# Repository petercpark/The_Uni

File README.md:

# The Uni Board
The uni-body split ortholinear keyboard for stenography, or the Uni for short. By Peter C Park. This is the pro micro version. I used KiCad Nightly Release so the kicad files are not compatible with older version.

Buy it now at [StenoKeyboards.com](https://www.stenokeyboards.com/).

## Product
If you are going DIY with this, here are the materials you need:
* The Uni PCB x 1 (diodes will come pre-assembled)
* Arduino Pro Micro x 1
* Switches x 28
* Keycaps x 28
* Willingness to solder x 1

If you want me to assemble here are the materials you need:
* money

## Arduino
The arduino you should use is the Pro Micro. You can also use other microcontrollers with same footprints such as the Elite C.

## Switches
Nearly any switch is compatible with the v2. The board has a footprint that accomodates for mx, alps, and choc v1 style switches.

## Keycaps
The best keycaps to use are the OEM R3 keycaps with one of the rows inverted to reduce the gap in the middle.
I used to recommend 3d printing your caps but OEM R3 caps are better. There are other flat keycaps for mx style switches at pimpmykeyboard.com called f10 keycaps. There is also a slightly less flatter version called the G20 keycaps on their store and people have used them for steno.

## Soldering
All you have to solder are the switches and pro micro if you get the pcb with the diodes assembled. If not you'll have to solder the smd diodes yourself. Check the BOM file for the necessary materials.

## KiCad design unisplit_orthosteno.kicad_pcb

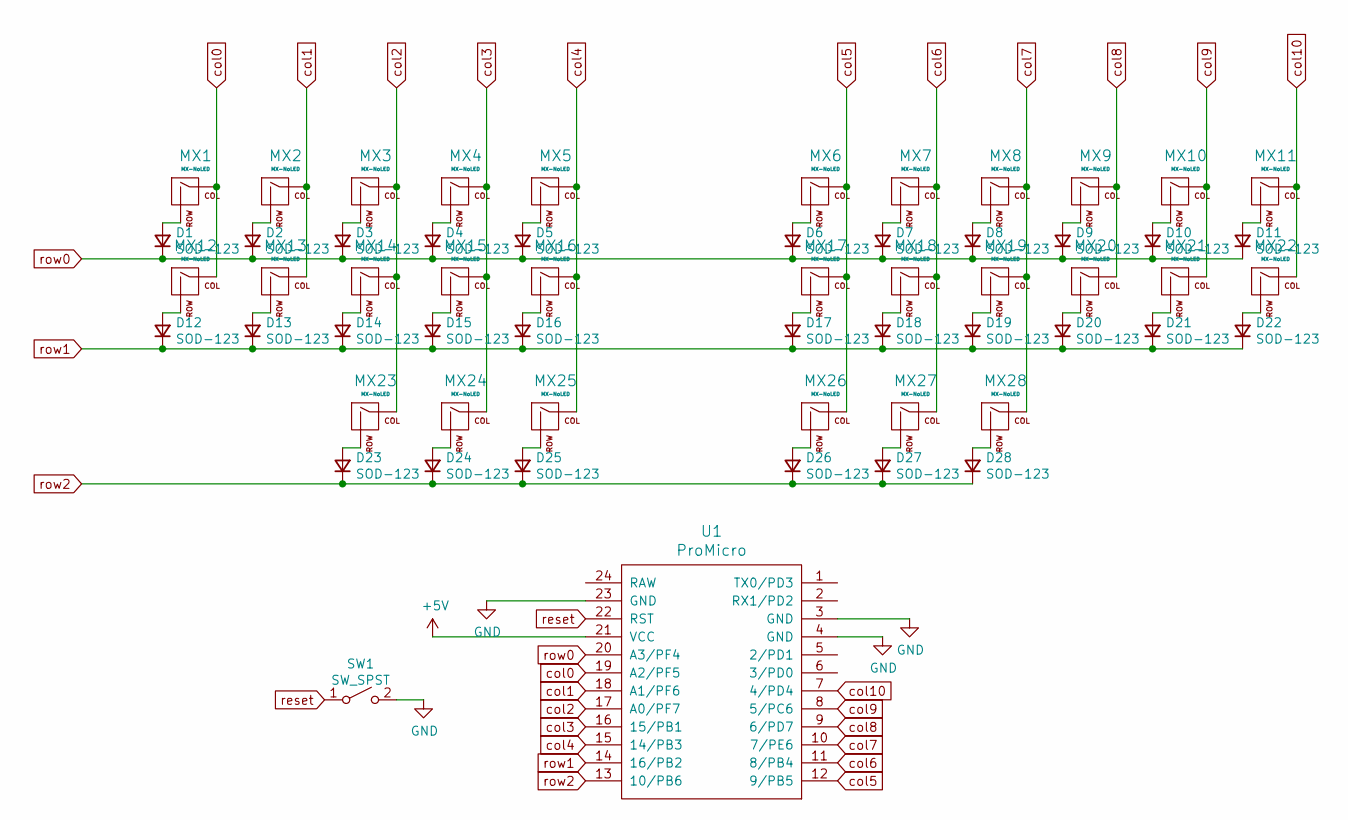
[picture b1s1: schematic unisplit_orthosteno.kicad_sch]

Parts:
D1, D2, D3, D4, D5, D6, D7, D8, D9, D10, D11, D12, D13, D15, D16, D17, D18, D19, D20, D21, D22, D23, D24, D25, D26, D27, D28: SOD-123; D_SOD123; LCSC C81598
D14: SOD-123; D_SOD123
MX1, MX2, MX3, MX4, MX5, MX6, MX7, MX8, MX9, MX10, MX11, MX12, MX13, MX14, MX15, MX16, MX17, MX18, MX19, MX20, MX21, MX22, MX23, MX24, MX25, MX26, MX27, MX28: MX-NoLED; MX-Alps-Choc-1U-NoLED
SW1: SW_SPST; SW_SPST_TL3342
U1: ProMicro; ArduinoProMicro

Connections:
+5V: U1.21 (VCC)
GND: SW1.2 (B), U1.3 (GND), U1.4 (GND), U1.23 (GND)
unnamed: D1.2 (A), MX1.2 (ROW)
unnamed: D2.2 (A), MX2.2 (ROW)
unnamed: D3.2 (A), MX3.2 (ROW)
unnamed: D4.2 (A), MX4.2 (ROW)
unnamed: D5.2 (A), MX5.2 (ROW)
unnamed: D6.2 (A), MX6.2 (ROW)
unnamed: D7.2 (A), MX7.2 (ROW)
unnamed: D8.2 (A), MX8.2 (ROW)
unnamed: D9.2 (A), MX9.2 (ROW)
unnamed: D10.2 (A), MX10.2 (ROW)
unnamed: D11.2 (A), MX11.2 (ROW)
unnamed: D12.2 (A), MX12.2 (ROW)
unnamed: D13.2 (A), MX13.2 (ROW)
unnamed: D14.2 (A), MX14.2 (ROW)
unnamed: D15.2 (A), MX15.2 (ROW)
unnamed: D16.2 (A), MX16.2 (ROW)
unnamed: D17.2 (A), MX17.2 (ROW)
unnamed: D18.2 (A), MX18.2 (ROW)
unnamed: D19.2 (A), MX19.2 (ROW)
unnamed: D20.2 (A), MX20.2 (ROW)
unnamed: D21.2 (A), MX21.2 (ROW)
unnamed: D22.2 (A), MX22.2 (ROW)
unnamed: D23.2 (A), MX23.2 (ROW)
unnamed: D24.2 (A), MX24.2 (ROW)
unnamed: D25.2 (A), MX25.2 (ROW)
unnamed: D26.2 (A), MX26.2 (ROW)
unnamed: D27.2 (A), MX27.2 (ROW)
unnamed: D28.2 (A), MX28.2 (ROW)
col0: MX1.1 (COL), MX12.1 (COL), U1.19 (A2/PF5)
col1: MX2.1 (COL), MX13.1 (COL), U1.18 (A1/PF6)
col2: MX3.1 (COL), MX14.1 (COL), MX23.1 (COL), U1.17 (A0/PF7)
col3: MX4.1 (COL), MX15.1 (COL), MX24.1 (COL), U1.16 (15/PB1)
col4: MX5.1 (COL), MX16.1 (COL), MX25.1 (COL), U1.15 (14/PB3)
col5: MX6.1 (COL), MX17.1 (COL), MX26.1 (COL), U1.12 (9/PB5)
col6: MX7.1 (COL), MX18.1 (COL), MX27.1 (COL), U1.11 (8/PB4)
col7: MX8.1 (COL), MX19.1 (COL), MX28.1 (COL), U1.10 (7/PE6)
col8: MX9.1 (COL), MX20.1 (COL), U1.9 (6/PD7)
col9: MX10.1 (COL), MX21.1 (COL), U1.8 (5/PC6)
col10: MX11.1 (COL), MX22.1 (COL), U1.7 (4/PD4)
reset: SW1.1 (A), U1.22 (RST)
row0: D1.1 (K), D2.1 (K), D3.1 (K), D4.1 (K), D5.1 (K), D6.1 (K), D7.1 (K), D8.1 (K), D9.1 (K), D10.1 (K), D11.1 (K), U1.20 (A3/PF4)
row1: D12.1 (K), D13.1 (K), D14.1 (K), D15.1 (K), D16.1 (K), D17.1 (K), D18.1 (K), D19.1 (K), D20.1 (K), D21.1 (K), D22.1 (K), U1.14 (16/PB2)
row2: D23.1 (K), D24.1 (K), D25.1 (K), D26.1 (K), D27.1 (K), D28.1 (K), U1.13 (10/PB6)

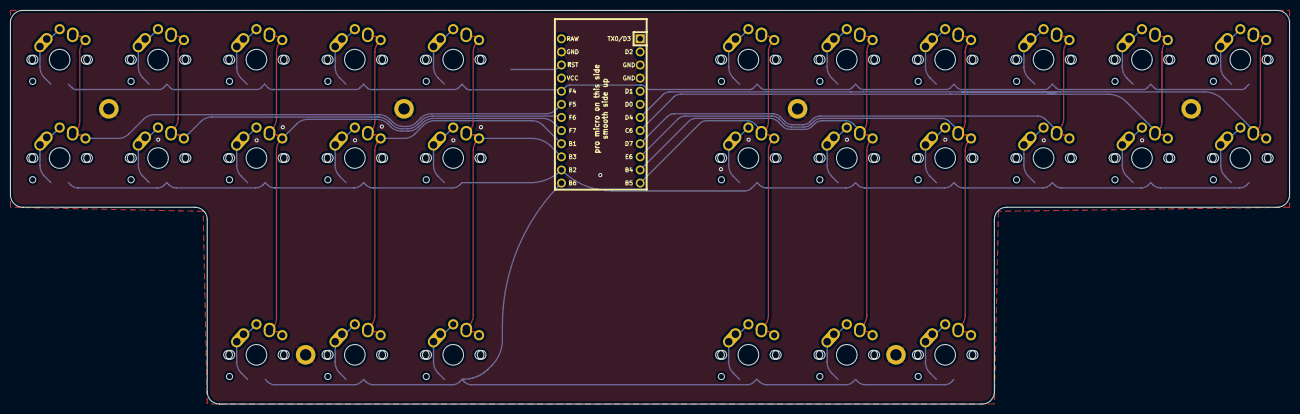
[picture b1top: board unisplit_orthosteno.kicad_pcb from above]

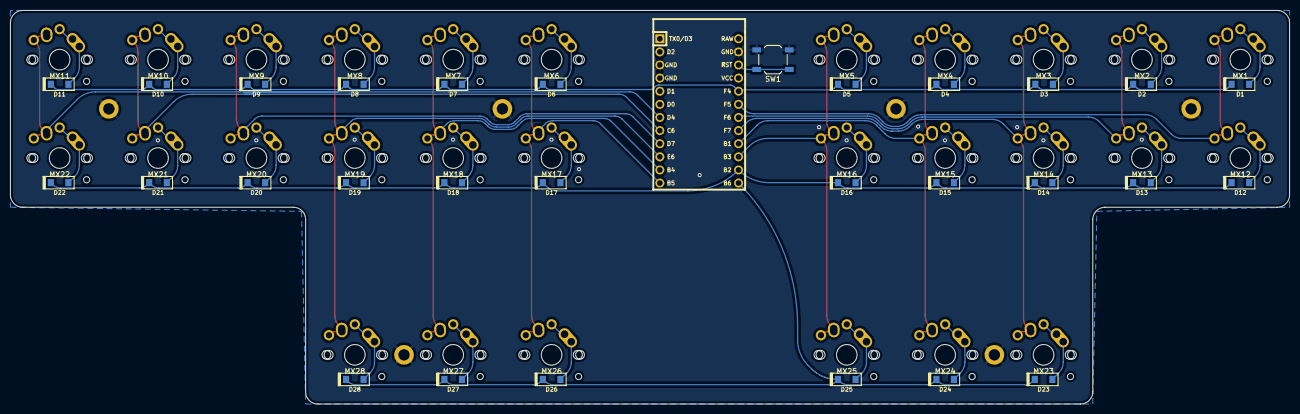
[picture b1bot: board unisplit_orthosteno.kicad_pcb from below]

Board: 2 copper layers, 247.6 x 76.2 mm, 58 parts (30 on the bottom side), 44 nets.

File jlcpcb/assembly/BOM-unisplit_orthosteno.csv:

Comment,Designator,Footprint,LCSC
SW_SPST,SW1,SW_SPST_TL3342,C318884
SOD-123,"D1,D10,D11,D12,D13,D14,D15,D16,D17,D18,D19,D2,D20,D21,D22,D23,D24,D25,D26,D27,D28,D3,D4,D5,D6,D7,D8,D9",D_SOD123,C81598

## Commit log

2021-01-21 add sumodules (symbols and footprints)
2021-01-21 symbols and footprints
2021-01-21 ai03 library import for symbols and footprints
2021-01-21 add keebio library
2021-01-21 get rid of unwanted submodule
2021-01-21 all components and footprints added
2021-01-21 finally found pro micro symbol from keebio
2021-01-21 assign footprints and do some organizing
2021-01-22 finished routing but possible problem in column 3 and 4 which I asked and reddit
2021-01-23 re route and change layout per suggestions from plover discord
2021-01-23 generate gerbers
2021-01-23 finalize gerbers and create bom and place files for jlcpcb
2021-01-24 add uni name on the pcb
2021-01-24 still working on making case files, but added a read me
2021-01-26 create rough design of case and plate, but it is not the correct measurments
2021-01-30 update case files, now the cases should be okay, case may be a bit tight so scaling up like 0.001 percent might help when 3d printing it
2021-01-30 add image of 3d printed keycaps
2021-01-30 add single cap picture
2021-01-30 add license
2021-01-31 update case files by giving a little bit of clearance
2021-01-31 add image of layout
2021-02-13 add some pics
2021-02-16 add firmware file
2021-02-16 zip file of hex
2021-02-16 add source code of firmware
2021-02-16 change layout image
2021-02-17 add guide folder
2021-02-17 add diy.md
2021-02-17 pro micro image add
2021-02-17 soldering pro micro picture
2021-02-17 qmk toolbox setup image
2021-02-20 add image of keycaps and change case
2021-02-24 revert back to slightly tighter case fit, and fix misalignment
2021-02-24 stl files for case revert back to slightly tighter
2021-02-24 make case/sleeve fit exactly the same as the pcb, no tolerances
2021-02-25 add files for keycaps
2021-02-26 add split case files for easy printing
2021-02-26 add case-info.md file
2021-03-03 add mounting holes to the uni pcb, also create a back plate folder in cases folder
2021-03-04 back plate move to reference folder
2021-03-08 backplate design
2021-03-08 add back plate screen shot
2021-03-10 add rubber feet placement image
2021-03-31 curvy trace and add reset
2021-04-01 save backplate file
2021-04-01 get rid of backplate
2021-04-01 add backplate
2021-04-01 change rubber feet placement in guide
2021-04-02 gregg shorthand
2021-04-02 make a no overlap mx-alp-choc footprint
2021-04-04 create plate and case designs
2021-04-05 artwork
2021-04-06 fix fatal diode error
2021-04-06 change name guide to docs
2021-04-08 plate stuff
2021-04-08 qmk folder is now in separate repository
2021-04-09 add tooling and order number
2021-04-09 blep
2021-04-13 3dp case with ceiling and fillet
2021-04-13 add more mounting holes
2021-04-15 get rid of extra nuisance mounting holes
2021-04-20 update keycap, also add some photos
2021-04-22 keycaps
2021-04-27 update gerbers.
2021-05-05 docs
2021-05-15 update commit
2021-05-28 gerbers and backplate
2021-06-04 step file
2021-06-08 add pictures and update
2021-06-12 make choc keycap model
2021-06-21 caps update
2021-08-09 gitignore
2024-11-16 add schematic
